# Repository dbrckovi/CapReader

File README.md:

# CapReader
Arduino Nano based capacitance meter

# Brief description:
Can measure capacitors from 1nF upwards.

When button is pressed, continuously discharges and charges the capacitor through different resistors, measuring time it takes for a capacitor to charge up to 63.2%.
When the value is measured, discharges the capacitor and value is displayed on LCD.

Button must be held until measurement is finished.

# Problems:
 
 - Measuring capacitors of about 10uF takes longer than 100+F. Resistor values must be calibrated to avoid these jumps in measurement time
 - Measurements which took < 10ms are discarded. This value is probably too high.

# Ideas:
 - Try using micros instead of millis
 - Try replacing 10M resistor with 100M to see if pF capacitances can be measured.
 - Try adding 220 Ohm resistor to see if really big capacitors can be measured in reasonable time.

# Todo:
 - Add code comments
 - Add schematic
 - Write proper readme
 - Choose proper license

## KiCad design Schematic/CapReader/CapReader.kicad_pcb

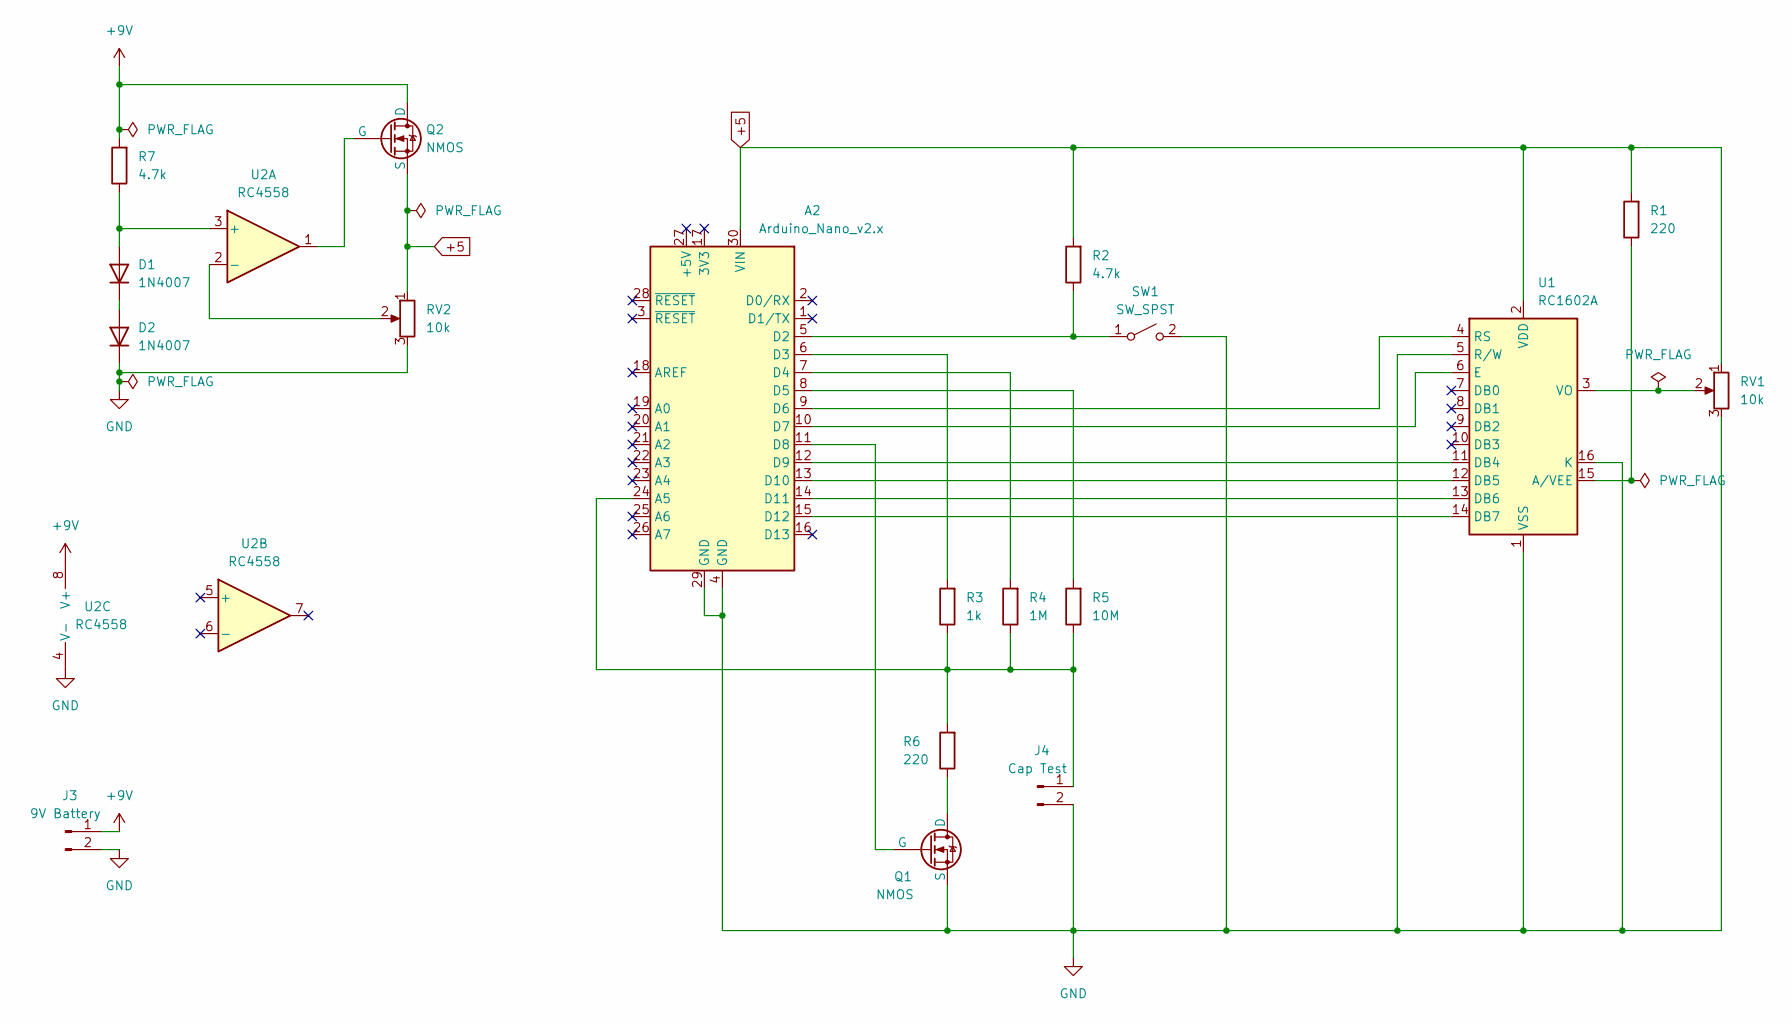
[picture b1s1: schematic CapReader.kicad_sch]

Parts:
A2: Arduino_Nano_v2.x; Arduino_Nano
D1, D2: 1N4007; D_DO-41_SOD81_P10.16mm_Horizontal
J3: 9V Battery; TestPoint_2Pads_Pitch2.54mm_Drill0.8mm
J4: Cap Test; TestPoint_2Pads_Pitch2.54mm_Drill0.8mm
Q1, Q2: NMOS; TO-220-3_Vertical
R1, R6: 220; R_Axial_DIN0309_L9.0mm_D3.2mm_P12.70mm_Horizontal
R2, R7: 4.7k; R_Axial_DIN0309_L9.0mm_D3.2mm_P12.70mm_Horizontal
R3: 1k; R_Axial_DIN0309_L9.0mm_D3.2mm_P12.70mm_Horizontal
R4: 1M; R_Axial_DIN0309_L9.0mm_D3.2mm_P12.70mm_Horizontal
R5: 10M; R_Axial_DIN0309_L9.0mm_D3.2mm_P12.70mm_Horizontal
RV1, RV2: 10k; Potentiometer_Bourns_3386F_Vertical
SW1: SW_SPST; JWT_A3963_1x02_P3.96mm_Vertical
U1: RC1602A
U2: RC4558; DIP-8_W7.62mm_Socket

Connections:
+5: A2.30 (VIN), Q2.3 (S), R1.2, R2.2, RV1.1, RV2.1, U1.2 (VDD)
+9V: J3.1, Q2.1 (D), R7.2, U2.8 (V+)
GND: A2.4 (GND), A2.29 (GND), D2.1 (K), J3.2, J4.2, Q1.3 (S), RV1.3, RV2.3, SW1.2 (B), U1.1 (VSS), U1.5 (R/W), U1.16 (K), U2.4 (V-)
unnamed: A2.24 (A5), J4.1, R3.1, R4.1, R5.1, R6.2
unnamed: A2.5 (D2), R2.1, SW1.1 (A)
unnamed: A2.6 (D3), R3.2
unnamed: A2.7 (D4), R4.2
unnamed: A2.8 (D5), R5.2
unnamed: A2.9 (D6), U1.4 (RS)
unnamed: A2.10 (D7), U1.6 (E)
unnamed: A2.11 (D8), Q1.2 (G)
unnamed: A2.12 (D9), U1.11 (DB4)
unnamed: A2.13 (D10), U1.12 (DB5)
unnamed: A2.14 (D11), U1.13 (DB6)
unnamed: A2.15 (D12), U1.14 (DB7)
unnamed: D1.2 (A), R7.1, U2.3 (+)
unnamed: D1.1 (K), D2.2 (A)
unnamed: Q1.1 (D), R6.1
unnamed: Q2.2 (G), U2.1
unnamed: R1.1, U1.15 (A/VEE)
unnamed: RV1.2, U1.3 (VO)
unnamed: RV2.2, U2.2 (-)

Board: 2 copper layers, 19 parts (0 on the bottom side), 22 nets, no tracks yet.

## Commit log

2023-06-03 Initial commit. It works. No documentation or comments yet
2023-06-03 Quick README
2023-06-08 Measuring micros instead of millis. Using CHARGE_VALUE value instead of hardcoded
2023-06-08 Added Kicad schematic
2023-10-14 Don't remember any more what was changed
